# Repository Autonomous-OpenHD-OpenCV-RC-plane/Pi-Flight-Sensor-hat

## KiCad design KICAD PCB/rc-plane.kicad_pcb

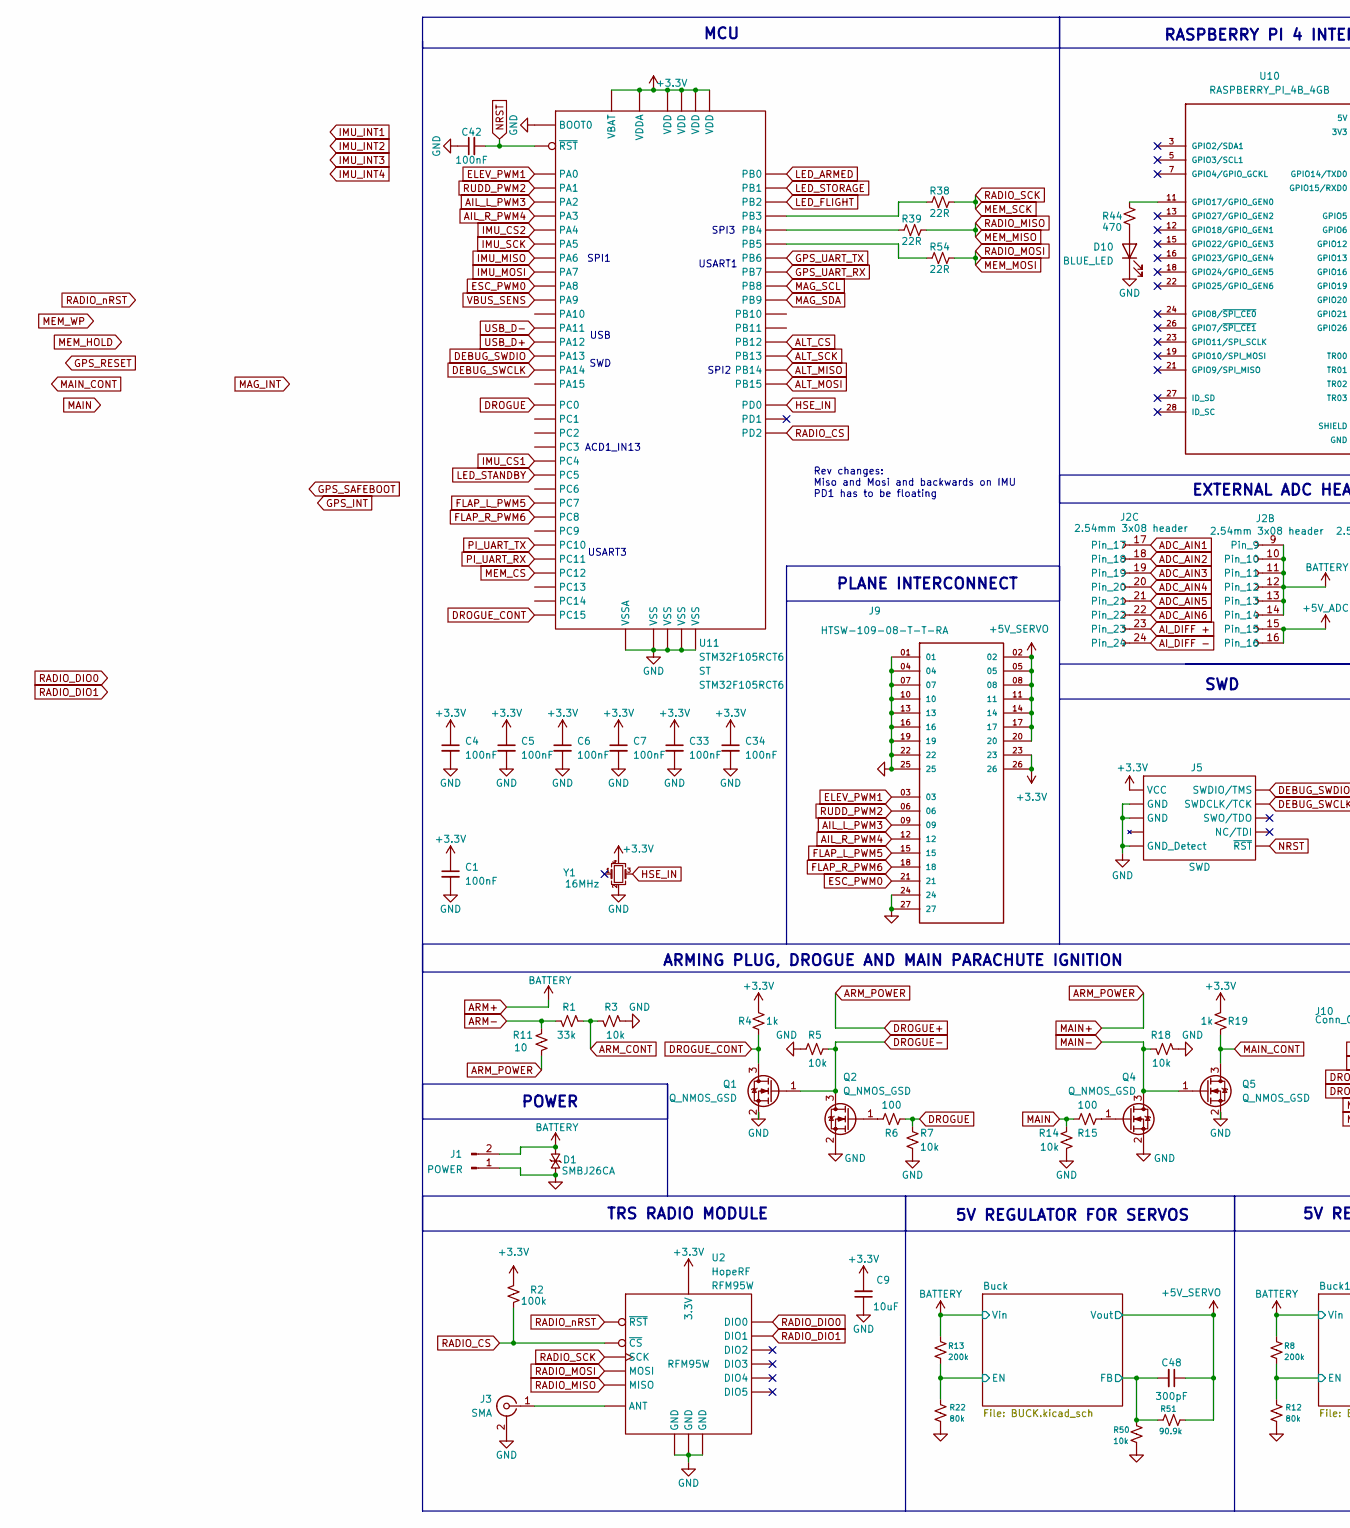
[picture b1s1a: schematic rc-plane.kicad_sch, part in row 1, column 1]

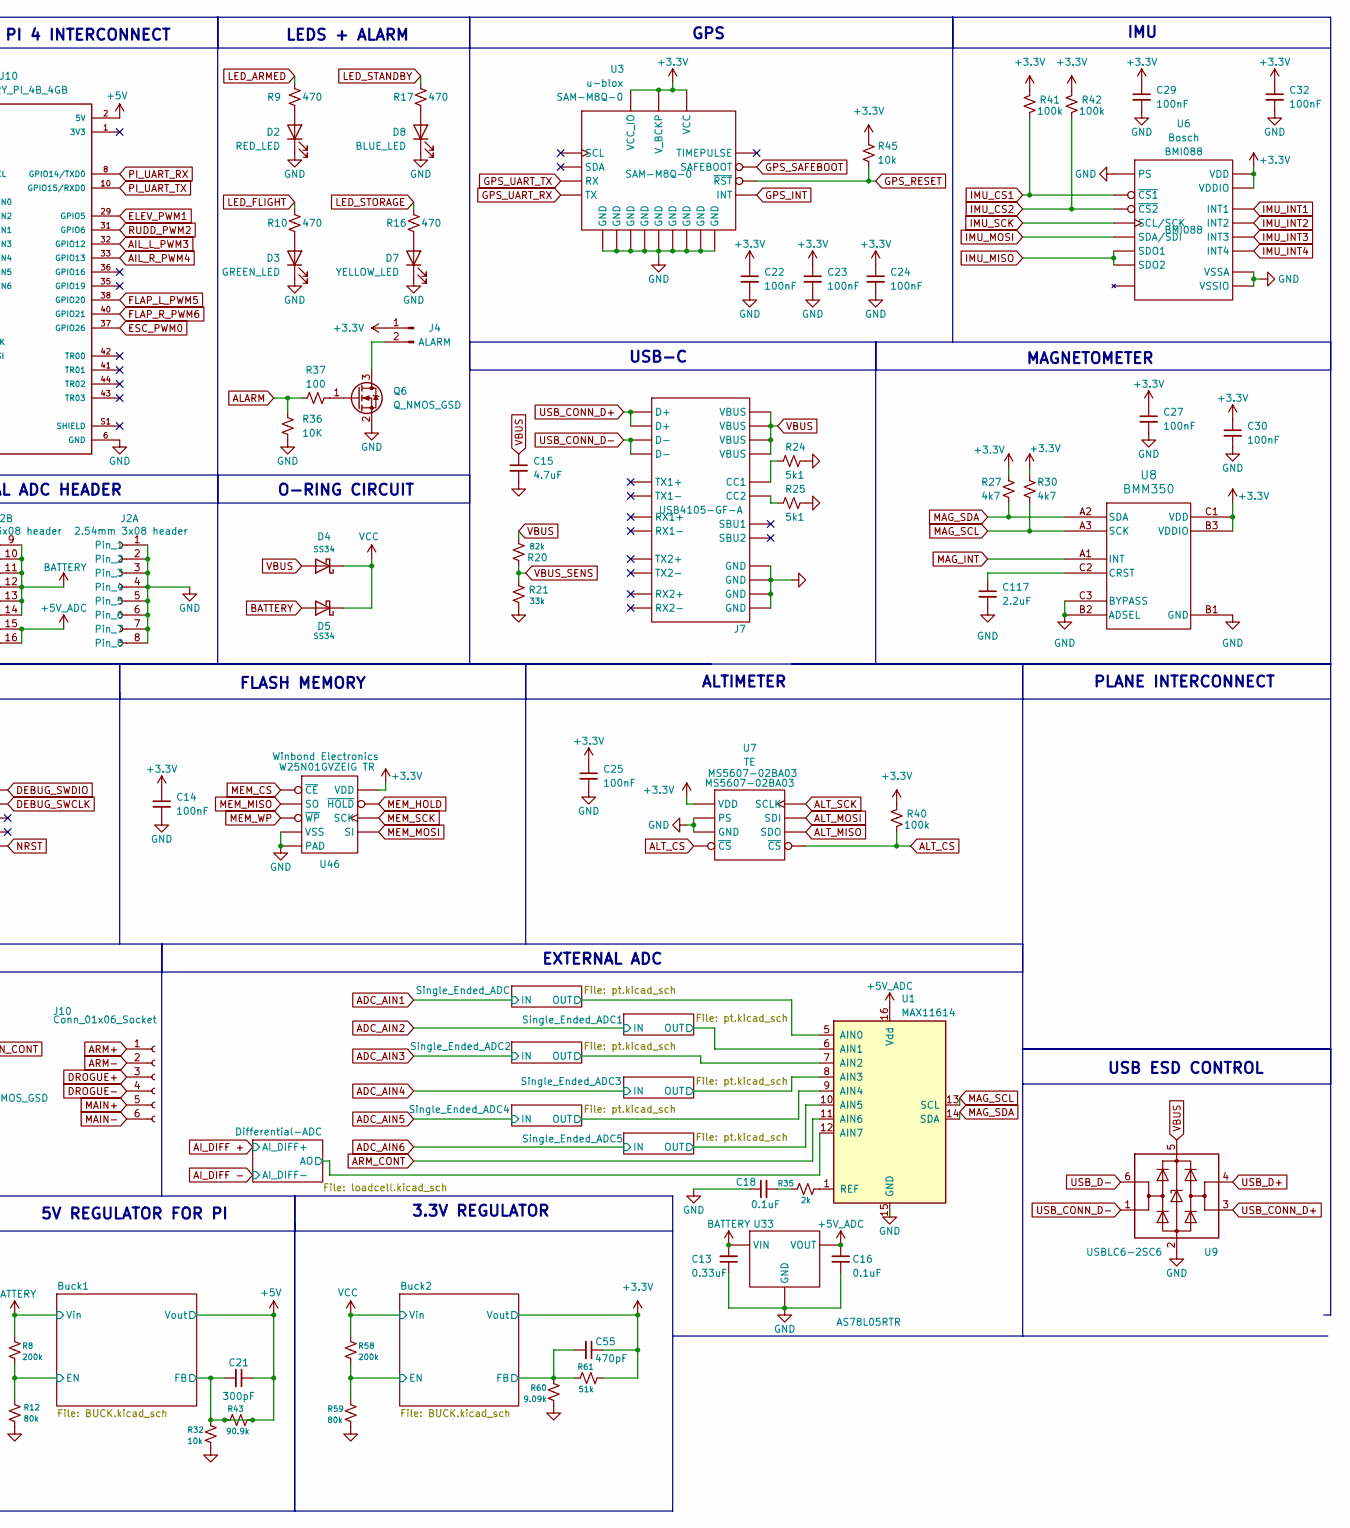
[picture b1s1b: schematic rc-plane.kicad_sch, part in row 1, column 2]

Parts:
C1, C4, C5, C6, C7, C14, C22, C23, C24, C25, C29, C32, C33, C34, C42: 100nF; C_0603_1608Metric; Part # Generic 0603 6.3V 100nF X7R MLCC
C9: 10uF; C_0603_1608Metric; Part # Generic 0603 6.3V 100nF X7R MLCC
C13: 0.33uF; C_0603_1608Metric; Part # Generic 22uF 35V X5R 1206 MLCC
C15: 4.7uF; C_0603_1608Metric; Part # Generic 0603 6.3V 4.7uF X7R MLCC
C16, C18: 0.1uF; C_0603_1608Metric; Part # Generic 22uF 35V X5R 1206 MLCC
C21, C48: 300pF; C_0603_1608Metric; Part # Generic 0603 6.3V 100nF X7R MLCC
C27, C30: 100nF; C_0402_1005Metric; Part # Generic CAP CER 0.1UF 6.3V X7R 0402
C55: 470pF; C_0603_1608Metric; Part # Generic 0603 6.3V 100nF X7R MLCC
C117: 2.2uF; C_0402_1005Metric; Part # Generic CAP CER 0.1UF 6.3V X7R 0402
D1: SMBJ26CA; D_SMB; PARTREV I2102; DigiKey_Part_Number SMBJ26CAFSCT-ND
D2: RED_LED; D_0603_1608Metric; Part # Generic Green LED
D3: GREEN_LED; D_0603_1608Metric; Part # Generic Green LED
D4, D5: SS34; D_SMA; Part # SS34
D7: YELLOW_LED; D_0603_1608Metric; Part # Generic Yellow LED
D8, D10: BLUE_LED; D_0603_1608Metric; Part # Generic Green LED
J1: POWER; AMASS_XT60PW-M_1x02_P7.20mm_Horizontal; Part # XT60PW-F
J2: 2.54mm 3x08 header; HX PZ2.54-3x8P ZZ 3x08 2.54mm THT header; Part # HX PZ2.54-3x8P ZZ
J3: SMA; SMA_Molex_73251-2200_Horizontal; Part # 0732512200
J4: ALARM; XDCR_SMT-0540-S-R; Part # CMI-0955-03TH
J5: SWD; PinHeader_2x05_P1.27mm_Vertical_SMD; Part # 4048
J7: USB4105-GF-A; USB_C_Receptacle_GCT_USB4105-xx-A_16P_TopMnt_Horizontal; Part # USB4105-GF-A
J9: HTSW-109-08-T-T-RA; SAMTEC_HTSW-109-08-T-T-RA; PARTREV R
J10: Conn_01x06_Socket; TerminalBlock_Xinya_XY308-2.54-6P_1x06_P2.54mm_Horizontal
Q1, Q2, Q4, Q5, Q6: Q_NMOS_GSD; TSOT-23; Part # WST3408
R1: 33k; R_0603_1608Metric; Part # Generic 0603 1k 1% Resistor
R2, R40, R41, R42: 100k; R_0603_1608Metric; Part # Generic 0603 1k 1% Resistor
R3: 10k; R_0603_1608Metric; Part # Generic 0603 3.3k 1% Resistor
R4, R19: 1k; R_0603_1608Metric; Part # Generic 0603 1k 1% Resistor
R5, R7, R14, R18: 10k; R_0603_1608Metric; Part # Generic 0603 10k 1% Resistor
R6, R15: 100; R_0603_1608Metric; Part # Generic 0603 100 1% Resistor
R8, R13, R58: 200k; R_0603_1608Metric
R9, R10, R16, R17, R44: 470; R_0603_1608Metric; Part # Generic 0603 470 1% Resistor
R11: 10; R_0603_1608Metric; Part # Generic 0603 1k 1% Resistor
R12, R22, R59: 80k; R_0603_1608Metric
R20: 82k; R_0603_1608Metric; Part # Generic 0603 33k 1% Resistor
R21: 33k; R_0603_1608Metric; Part # Generic 0603 82k 1% Resistor
R24, R25: 5k1; R_0603_1608Metric; Part # Generic 0603 5.1k 1% Resistor
R27, R30: 4k7; R_0402_1005Metric; Part # Generic RES SMD 4.7K OHM 1% 1/4W 0402
R32, R45, R50: 10k; R_0603_1608Metric
R35: 2k; R_0603_1608Metric
R36: 10K; R_0402_1005Metric; Part # Generic RES SMD 10K OHM 1% 1/4W 0402
R37: 100; R_0402_1005Metric; Part # Generic RES SMD 100 OHM 1% 1/4W 0402
R38, R39, R54: 22R; R_0402_1005Metric; Part # Generic RES SMD 4.7K OHM 1% 1/4W 0402
R43, R51: 90.9k; R_0603_1608Metric
R60: 9.09k; R_0603_1608Metric
R61: 51k; R_0603_1608Metric
U1: MAX11614; QSOP-16_3.9x4.9mm_P0.635mm
U2: RFM95W; Part # RFM95W
U3: SAM-M8Q-0; ublox_SAM-M8Q; Part # SAM-M8Q-0
U6: BMI088; Part # BMI088
U7: MS5607-02BA03; MS5607-02BA; Part # MS5607-02BA03
U8: BMM350; Part # BMM350
U9: USBLC6-2SC6; SOT-23-6; Part # USBLC6-2SC6
U10: RASPBERRY_PI_4B_4GB; MODULE_RASPBERRY_PI_4B_4GB; PARTREV 4
U11: STM32F105RCT6; LQFP-64_10x10mm_P0.5mm; Part # STM32F105RCT6
U33: AS78L05RTR; SOT-89-3
U46: W25N01GVZEIG TR; WSON-8-1EP_8x6mm_P1.27mm_EP3.4x4.3mm; Part # W25N01GVZEIG TR
Y1: 16MHz; Crystal_SMD_2520-4Pin_2.5x2.0mm; Part # ECS-1633-120-BN-TR

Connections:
+3.3V: C1.1, C4.1, C5.1, C6.1, C7.1, C9.2, C14.1, C22.1, C23.1, C24.1, C25.1, C27.1, C29.1, C30.1, C32.1, C33.1, C34.1, C55.1, J4.1, J5.1 (VCC), J9.23, J9.26, R2.2, R4.1, R19.1, R27.1, R30.1, R40.2, R41.2, R42.2, R45.1, R61.2, U2.13 (3.3V), U3.2 (VCC_IO), U3.3 (V_BCKP), U3.17 (VCC), U6.3 (VDD), U6.11 (VDDIO), U7.1 (VDD), U8.B3 (VDDIO), U8.C1 (VDD), U11.1 (VBAT), U11.13 (VDDA), U11.19 (VDD), U11.32 (VDD), U11.48 (VDD), U11.64 (VDD), U46.8 (VDD), Y1.4; also elsewhere on the board
+5V_ADC: C16.1, J2.15, J2.16, U1.16 (Vdd), U33.3 (VOUT); also elsewhere on the board
+5V_SERVO: C48.1, J9.02, J9.05, J9.08, J9.11, J9.14, J9.17, J9.20, R51.2; also elsewhere on the board
/Buck1/EN: R8.2, R12.1; also elsewhere on the board
/Buck2/EN: R58.2, R59.1; also elsewhere on the board
/Buck2/FB: C55.2, R60.1, R61.1; also elsewhere on the board
/Buck/EN: R13.2, R22.1; also elsewhere on the board
/Buck/FB: C48.2, R50.1, R51.1; also elsewhere on the board
/Differential-ADC/AO: U1.12 (AIN7); also elsewhere on the board
/Single_Ended_ADC1/OUT: U1.6 (AIN1); also elsewhere on the board
/Single_Ended_ADC2/OUT: U1.7 (AIN2); also elsewhere on the board
/Single_Ended_ADC3/OUT: U1.8 (AIN3); also elsewhere on the board
/Single_Ended_ADC4/OUT: U1.9 (AIN4); also elsewhere on the board
/Single_Ended_ADC5/OUT: U1.10 (AIN5); also elsewhere on the board
/Single_Ended_ADC/OUT: U1.5 (AIN0); also elsewhere on the board
ADC_AIN1: J2.17; also elsewhere on the board
ADC_AIN2: J2.18; also elsewhere on the board
ADC_AIN3: J2.19; also elsewhere on the board
ADC_AIN4: J2.20; also elsewhere on the board
ADC_AIN5: J2.21; also elsewhere on the board
ADC_AIN6: J2.22; also elsewhere on the board
AIL_L_PWM3: J9.09, U10.32 (GPIO12), U11.16 (PA2)
AIL_R_PWM4: J9.12, U10.33 (GPIO13), U11.17 (PA3)
AI_DIFF +: J2.23; also elsewhere on the board
AI_DIFF -: J2.24; also elsewhere on the board
ALARM: R36.2, R37.1
ALT_CS: R40.1, U7.4 (~CS), U7.5 (~CS), U11.33 (PB12)
ALT_MISO: U7.6 (SDO), U11.35 (PB14)
ALT_MOSI: U7.7 (SDI), U11.36 (PB15)
ALT_SCK: U7.8 (SCLK), U11.34 (PB13)
ARM+: C13.2, D1.1, D5.2 (A), J1.2, J2.9, J2.10, J2.11, J2.12, J2.13, J2.14, J10.1, R8.1, R13.1, U33.1 (VIN); also elsewhere on the board
ARM-: J10.2, R1.1, R11.2
ARM_CONT: R1.2, R3.1, U1.11 (AIN6)
ARM_POWER: J10.3, J10.5, R11.1
DEBUG_SWCLK: J5.4 (SWDCLK/TCK), U11.49 (PA14)
DEBUG_SWDIO: J5.2 (SWDIO/TMS), U11.46 (PA13)
DROGUE: R6.2, R7.1, U11.8 (PC0)
DROGUE-: J10.4, Q1.1 (G), Q2.3 (D), R5.1
DROGUE_CONT: Q1.3 (D), R4.2, U11.4 (PC15)
ELEV_PWM1: J9.03, U10.29 (GPIO5), U11.14 (PA0)
ESC_PWM0: J9.21, U10.37 (GPIO26), U11.41 (PA8)
FLAP_L_PWM5: J9.15, U10.38 (GPIO20), U11.38 (PC7)
FLAP_R_PWM6: J9.18, U10.40 (GPIO21), U11.39 (PC8)
GND: C1.2, C4.2, C5.2, C6.2, C7.2, C9.1, C13.1, C14.2, C15.2, C16.2, C18.1, C22.2, C23.2, C24.2, C25.2, C27.2, C29.2, C30.2, C32.2, C33.2, C34.2, C42.1, C117.2, D1.2, D2.1 (K), D3.1 (K), D7.1 (K), D8.1 (K), D10.1 (K), J1.1, J2.1, J2.2, J2.3, J2.4, J2.5, J2.6, J2.7, J2.8, J3.2 (Ext), J5.3 (GND), J5.5 (GND), J5.9 (GND_Detect), J7.A1 (GND), J7.A12 (GND), J7.B1 (GND), J7.B12 (GND), J9.01, J9.04, J9.07, J9.10, J9.13, J9.16, J9.19, J9.22, J9.24, J9.25, J9.27, Q1.2 (S), Q2.2 (S), Q4.2 (S), Q5.2 (S), Q6.2 (S), R3.2, R5.2, R7.2, R12.2, R14.2, R18.2, R21.1, R22.2, R24.1, R25.1, R32.2, R36.1, R50.2, R59.2, R60.2, U1.15 (GND), U2.1 (GND), U2.8 (GND), U2.10 (GND), U3.1 (GND), U3.4 (GND), U3.5 (GND), U3.6 (GND), U3.10 (GND), U3.11 (GND), U3.15 (GND), U3.16 (GND), U3.20 (GND), U6.4 (VSSA), U6.6 (VSSIO), U6.7 (PS), U7.2 (PS), U7.3 (GND), U8.B1 (GND), U8.B2 (ADSEL), U8.C3 (BYPASS), U9.2 (GND), U10.6 (GND), U10.9 (GND), U10.14 (GND), U10.20 (GND), U10.25 (GND), U10.30 (GND), U10.34 (GND), U10.39 (GND), U11.12 (VSSA), U11.18 (VSS), U11.31 (VSS), U11.47 (VSS), U11.60 (BOOT0), U11.63 (VSS), U33.2 (GND), U46.4 (VSS), U46.9 (PAD), Y1.2; also elsewhere on the board
GPS_INT: U3.19 (INT), U11.2 (PC13)
GPS_RESET: R45.2, U3.18 (~RST), U11.40 (PC9)
GPS_SAFEBOOT: U3.8 (SAFEBOOT), U11.3 (PC14)
GPS_UART_RX: U3.13 (TX), U11.59 (PB7)
GPS_UART_TX: U3.14 (RX), U11.58 (PB6)
HSE_IN: U11.5 (PD0), Y1.3
IMU_CS1: R41.1, U6.14 (~CS1), U11.24 (PC4)
IMU_CS2: R42.1, U6.5 (~CS2), U11.20 (PA4)
IMU_INT1: U6.16 (INT1)
IMU_INT2: U6.1 (INT2)
IMU_INT3: U6.12 (INT3)
IMU_INT4: U6.13 (INT4)
IMU_MISO: U6.10 (SDO2), U6.15 (SDO1), U11.22 (PA6)
IMU_MOSI: U6.9 (SDA/SDI), U11.23 (PA7)
IMU_SCK: U6.8 (SCL/SCK), U11.21 (PA5)
LED_ARMED: R9.1, U11.26 (PB0)
LED_FLIGHT: R10.1, U11.28 (PB2)
LED_STANDBY: R17.1, U11.25 (PC5)
LED_STORAGE: R16.1, U11.27 (PB1)
MAG_INT: U8.A1 (INT), U11.11 (PC3)
MAIN: R14.1, R15.1, U11.10 (PC2)
MAIN-: J10.6, Q4.3 (D), Q5.1 (G), R18.1
MAIN_CONT: Q5.3 (D), R19.2, U11.9 (PC1)
MEM_CS: U11.53 (PC12), U46.1 (~CE)
MEM_HOLD: U46.7 (~HOLD)
MEM_MISO: R39.2, U2.2 (MISO), U46.2 (SO)
MEM_MOSI: R54.2, U2.3 (MOSI), U46.5 (SI)
MEM_SCK: R38.2, U2.4 (SCK), U46.6 (SCK)
MEM_WP: U46.3 (~WP)
NRST: C42.2, J5.10 (~RST), U11.7 (~RST)
unnamed: C18.2, R35.1
unnamed: D2.2 (A), R9.2
unnamed: D3.2 (A), R10.2
unnamed: D7.2 (A), R16.2
unnamed: D8.2 (A), R17.2
unnamed: D10.2 (A), R44.2
unnamed: J3.1 (In), U2.9 (ANT)
unnamed: J4.2, Q6.3 (D)
unnamed: J7.A5 (CC1), R24.2
unnamed: J7.B5 (CC2), R25.2
unnamed: Q2.1 (G), R6.1
unnamed: Q4.1 (G), R15.2
unnamed: Q6.1 (G), R37.2
unnamed: R35.2, U1.1 (REF)
unnamed: C117.1, U8.C2 (CRST)
unnamed: R44.1, U10.11 (GPIO17/GPIO_GEN0)
unnamed: R38.1, U11.55 (PB3)
unnamed: R39.1, U11.56 (PB4)
unnamed: R54.1, U11.57 (PB5)
PI_UART_RX: U10.8 (GPIO14/TXD0), U11.52 (PC11)
PI_UART_TX: U10.10 (GPIO15/RXD0), U11.51 (PC10)
RADIO_CS: R2.1, U2.5 (~CS), U11.54 (PD2)
RADIO_DIO0: U2.14 (DIO0), U11.29 (PB10)
RADIO_DIO1: U2.15 (DIO1), U11.30 (PB11)
RADIO_nRST: U2.6 (~RST), U11.37 (PC6)
RUDD_PWM2: J9.06, U10.31 (GPIO6), U11.15 (PA1)
SCL: R30.2, U1.13 (SCL), U8.A3 (SCK), U11.61 (PB8)
SDA: R27.2, U1.14 (SDA), U8.A2 (SDA), U11.62 (PB9)
USB_CONN_D+: J7.A6 (D+), J7.B6 (D+), U9.3 (I/O2)
USB_CONN_D-: J7.A7 (D-), J7.B7 (D-), U9.1 (I/O1)
USB_D+: U9.4 (I/O2), U11.45 (PA12)
USB_D-: U9.6 (I/O1), U11.44 (PA11)
VBUS: C15.1, D4.2 (A), J7.A4 (VBUS), J7.A9 (VBUS), J7.B4 (VBUS), J7.B9 (VBUS), R20.1, U9.5 (VBUS)
VBUS_SENS: R20.2, R21.2, U11.42 (PA9)
VCC: D4.1 (K), D5.1 (K), R58.1; also elsewhere on the board

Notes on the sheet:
USART1
POWER
TRS RADIO MODULE
PLANE INTERCONNECT
USB ESD CONTROL
Rev changes: Miso and Mosi and backwards on IMU PD1 has to be floating
USART3
SWD
MCU
ALTIMETER
5V REGULATOR FOR SERVOS
SPI2
SWD
O-RING CIRCUIT
GPS
IMU
EXTERNAL ADC HEADER
MAGNETOMETER
FLASH MEMORY
RASPBERRY PI 4 INTERCONNECT
SPI1
USB-C
USB
LEDS + ALARM
ARMING PLUG, DROGUE AND MAIN PARACHUTE IGNITION
5V REGULATOR FOR PI
SPI3
ACD1_IN13
EXTERNAL ADC
3.3V REGULATOR

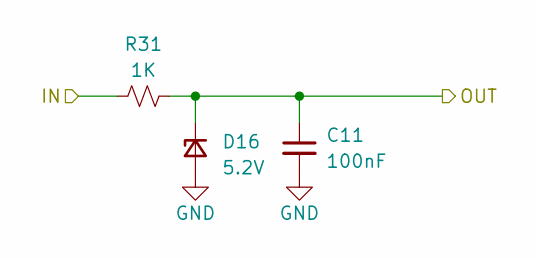
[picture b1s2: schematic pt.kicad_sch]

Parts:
C11: 100nF; C_0402_1005Metric; Part # Generic CAP CER 0.1UF 6.3V X7R 0402
D16: 5.2V; D_SOD-882; Part # BZT52C3V9LP-7
R31: 1K; R_0402_1005Metric; Part # Generic RES SMD 1K OHM 1% 1/16W 0402

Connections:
/Single_Ended_ADC/OUT: C11.1, D16.1 (K), R31.2; also elsewhere on the board
ADC_AIN1: R31.1; also elsewhere on the board
GND: C11.2, D16.2 (A); also elsewhere on the board

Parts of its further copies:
C2, C3, C8, C10, C12: 100nF; C_0402_1005Metric; Part # Generic CAP CER 0.1UF 6.3V X7R 0402
R23, R26, R28, R29, R33: 1K; R_0402_1005Metric; Part # Generic RES SMD 1K OHM 1% 1/16W 0402

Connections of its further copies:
/Single_Ended_ADC1/OUT: C2.1, R23.2; also elsewhere on the board
/Single_Ended_ADC2/OUT: C3.1, R26.2; also elsewhere on the board
/Single_Ended_ADC3/OUT: C8.1, R28.2; also elsewhere on the board
/Single_Ended_ADC4/OUT: C10.1, R29.2; also elsewhere on the board
/Single_Ended_ADC5/OUT: C12.1, R33.2; also elsewhere on the board
ADC_AIN2: R23.1; also elsewhere on the board
ADC_AIN3: R26.1; also elsewhere on the board
ADC_AIN4: R28.1; also elsewhere on the board
ADC_AIN5: R29.1; also elsewhere on the board
ADC_AIN6: R33.1; also elsewhere on the board
GND: C2.2, C3.2, C8.2, C10.2, C12.2; also elsewhere on the board

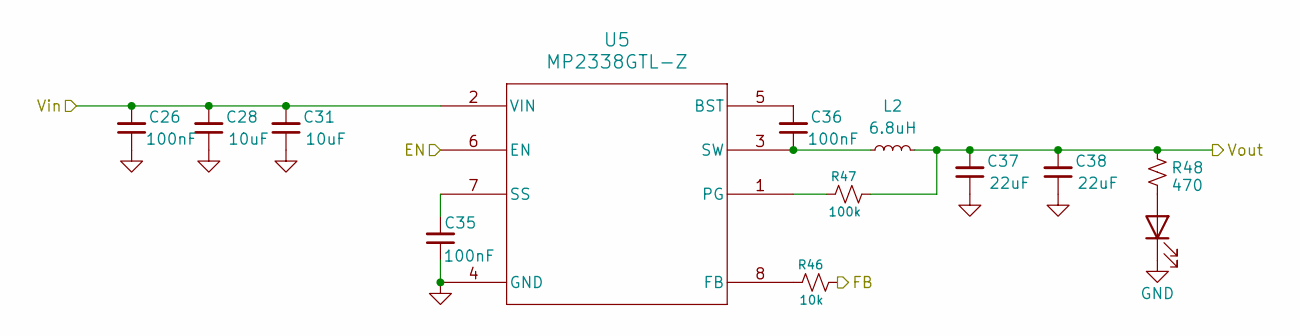
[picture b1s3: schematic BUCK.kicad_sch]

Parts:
C26, C35, C36: 100nF; C_0603_1608Metric; Part # Generic 0603 6.3V 100nF X7R MLCC
C28, C31: 10uF; C_0603_1608Metric; Part # Generic 0603 6.3V 100nF X7R MLCC
C37, C38: 22uF; C_0603_1608Metric; Part # Generic 0603 6.3V 100nF X7R MLCC
D11: BLUE_LED; D_0603_1608Metric; Part # Generic Green LED
L2: 6.8uH; IND_VLS6045EX-6R8M; Part # VLS6045EX-6R8M
R46: 10k; R_0603_1608Metric
R47: 100k; R_0603_1608Metric
R48: 470; R_0603_1608Metric; Part # Generic 0603 470 1% Resistor
U5: MP2338GTL-Z; SOT583_MP2338_MNP; Part # MP2338GTL-P

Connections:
/Buck1/EN: U5.6 (EN); also elsewhere on the board
ARM+: C26.2, C28.2, C31.2, U5.2 (VIN); also elsewhere on the board
GND: C26.1, C28.1, C31.1, C35.1, C37.1, C38.1, D11.1 (K), U5.4 (GND); also elsewhere on the board
unnamed: D11.2 (A), R48.2
unnamed: C36.2, U5.5 (BST)
unnamed: R46.1, U5.8 (FB)
unnamed: R47.1, U5.1 (PG)
unnamed: C35.2, U5.7 (SS)
unnamed: C36.1, L2.1, U5.3 (SW)

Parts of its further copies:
C39, C43, C44, C46, C51, C52: 100nF; C_0603_1608Metric; Part # Generic 0603 6.3V 100nF X7R MLCC
C40, C41, C49, C50: 10uF; C_0603_1608Metric; Part # Generic 0603 6.3V 100nF X7R MLCC
C45, C47, C53, C54: 22uF; C_0603_1608Metric; Part # Generic 0603 6.3V 100nF X7R MLCC
D12, D13: BLUE_LED; D_0603_1608Metric; Part # Generic Green LED
L3, L4: 6.8uH; IND_VLS6045EX-6R8M; Part # VLS6045EX-6R8M
R49, R53: 10k; R_0603_1608Metric
R52, R55: 100k; R_0603_1608Metric
R56, R57: 470; R_0603_1608Metric; Part # Generic 0603 470 1% Resistor
U12, U13: MP2338GTL-Z; SOT583_MP2338_MNP; Part # MP2338GTL-P

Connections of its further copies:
+3.3V: C53.2, C54.2, L4.2, R55.2, R57.1; also elsewhere on the board
+5V_SERVO: C45.2, C47.2, L3.2, R52.2, R56.1; also elsewhere on the board
/Buck2/EN: U13.6 (EN); also elsewhere on the board
/Buck2/FB: R49.2; also elsewhere on the board
/Buck/EN: U12.6 (EN); also elsewhere on the board
/Buck/FB: R53.2; also elsewhere on the board
ARM+: C39.2, C40.2, C41.2, U12.2 (VIN); also elsewhere on the board
GND: C39.1, C40.1, C41.1, C43.1, C45.1, C46.1, C47.1, C49.1, C50.1, C51.1, C53.1, C54.1, D12.1 (K), D13.1 (K), U12.4 (GND), U13.4 (GND); also elsewhere on the board
unnamed: D12.2 (A), R56.2
unnamed: D13.2 (A), R57.2
unnamed: C44.2, U12.5 (BST)
unnamed: R53.1, U12.8 (FB)
unnamed: R52.1, U12.1 (PG)
unnamed: C43.2, U12.7 (SS)
unnamed: C44.1, L3.1, U12.3 (SW)
unnamed: C52.2, U13.5 (BST)
unnamed: R49.1, U13.8 (FB)
unnamed: R55.1, U13.1 (PG)
unnamed: C51.2, U13.7 (SS)
unnamed: C52.1, L4.1, U13.3 (SW)
VCC: C46.2, C49.2, C50.2, U13.2 (VIN); also elsewhere on the board

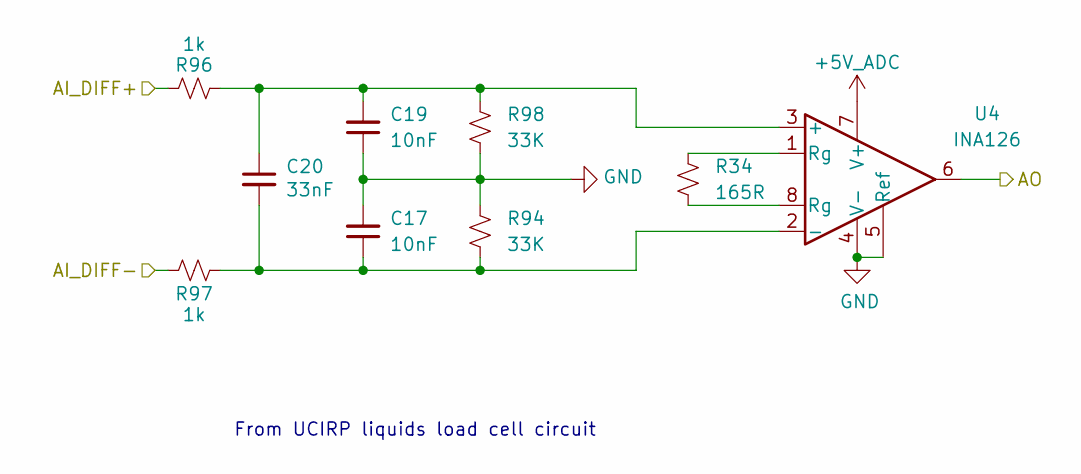
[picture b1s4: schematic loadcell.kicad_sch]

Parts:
C17, C19: 10nF; C_0603_1608Metric
C20: 33nF; C_0603_1608Metric
R34: 165R; R_0603_1608Metric; Part # Generic 33K 1% 0402 Resistor
R94, R98: 33K; R_0603_1608Metric; Part # Generic 33K 1% 0402 Resistor
R96, R97: 1k; R_0603_1608Metric
U4: INA126; SOIC-8_3.9x4.9mm_P1.27mm

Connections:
+5V_ADC: U4.7 (V+); also elsewhere on the board
/Differential-ADC/AO: U4.6; also elsewhere on the board
AI_DIFF +: R96.2; also elsewhere on the board
AI_DIFF -: R97.1; also elsewhere on the board
GND: C17.2, C19.1, R94.2, R98.1, U4.4 (V-), U4.5 (Ref); also elsewhere on the board
unnamed: R34.1, U4.8 (Rg)
unnamed: R34.2, U4.1 (Rg)
unnamed: C19.2, C20.1, R96.1, R98.2, U4.3 (+)
unnamed: C17.1, C20.2, R94.1, R97.2, U4.2 (-)

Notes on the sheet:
From UCIRP liquids load cell circuit

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
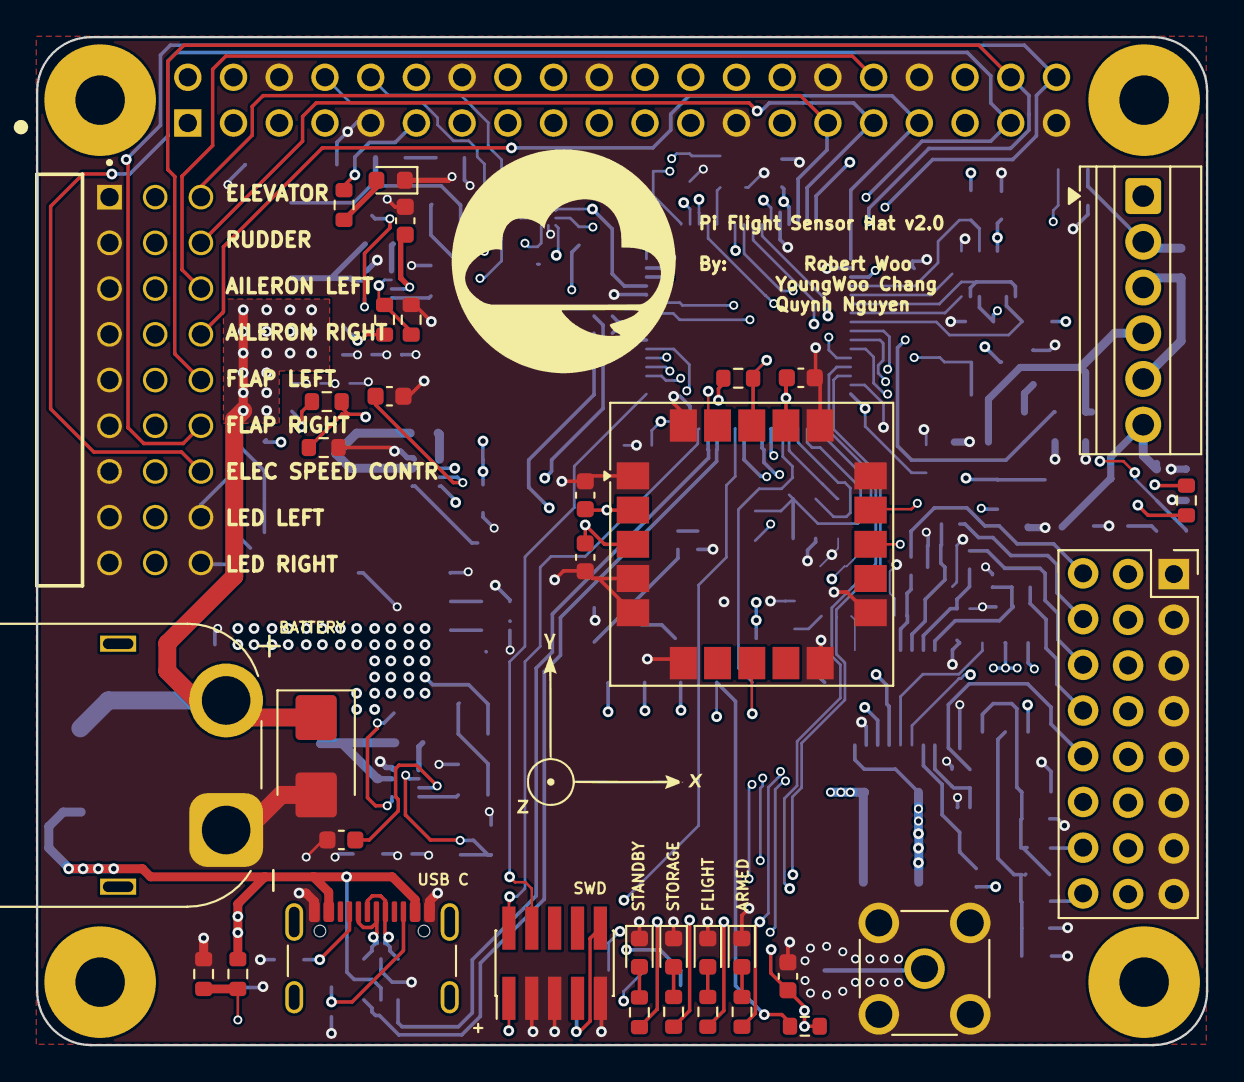
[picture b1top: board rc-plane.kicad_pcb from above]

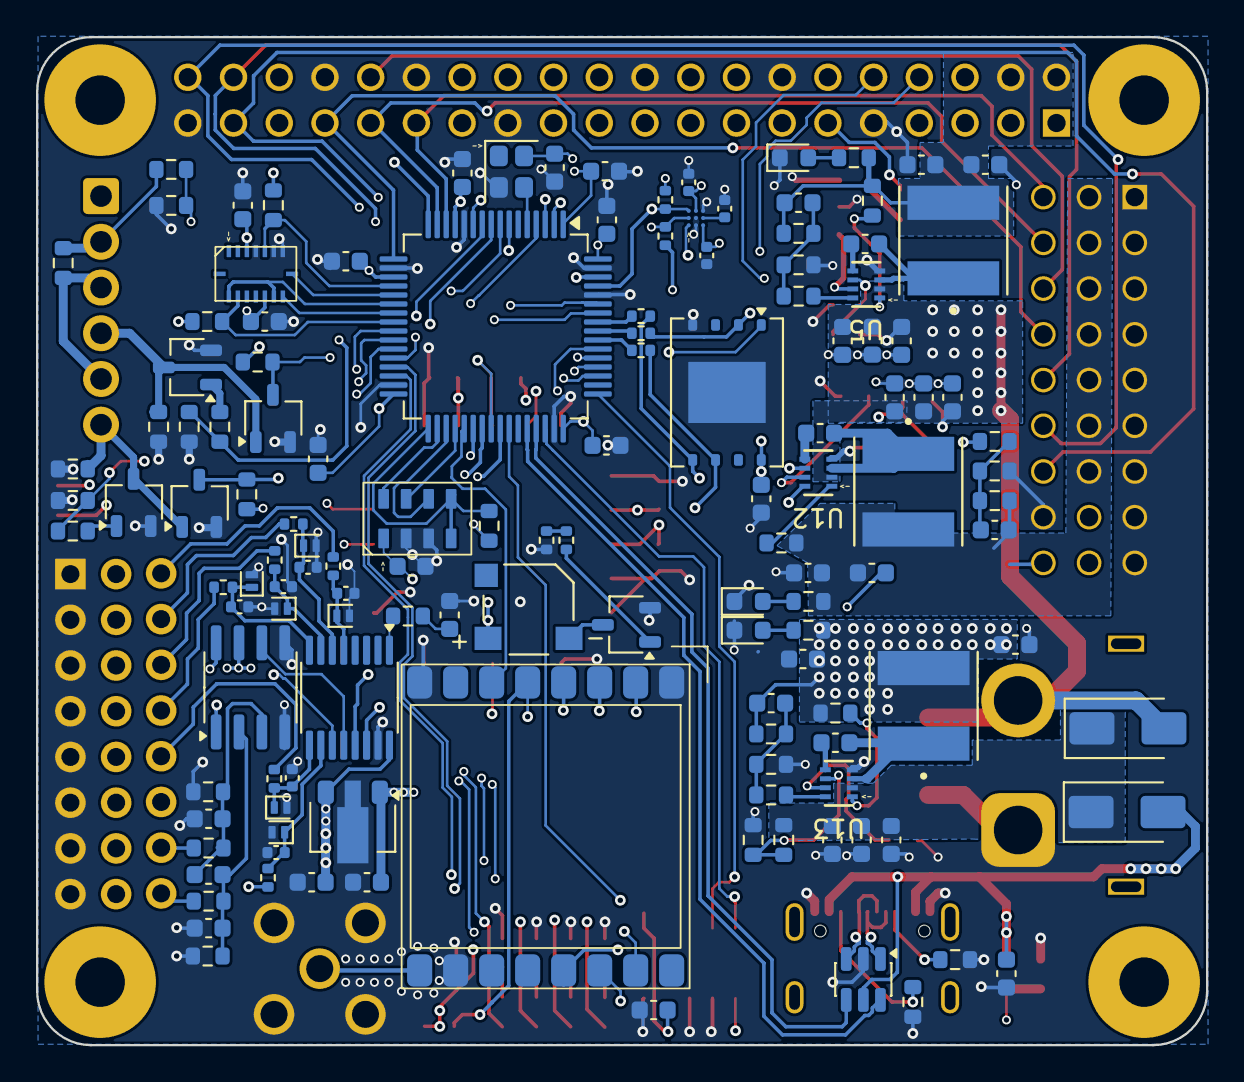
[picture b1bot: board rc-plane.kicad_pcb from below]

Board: 4 copper layers, 65.0 x 56.0 mm, 170 parts (134 on the bottom side), 127 nets.

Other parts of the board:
D6, D9, D14, D15, D17: 3.9V; D_SOD-882

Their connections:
/Single_Ended_ADC1/OUT: D6.1 (K); also elsewhere on the board
/Single_Ended_ADC2/OUT: D9.1 (K); also elsewhere on the board
/Single_Ended_ADC3/OUT: D14.1 (K); also elsewhere on the board
/Single_Ended_ADC4/OUT: D15.1 (K); also elsewhere on the board
/Single_Ended_ADC5/OUT: D17.1 (K); also elsewhere on the board
GND: D6.2 (A), D9.2 (A), D14.2 (A), D15.2 (A), D17.2 (A); also elsewhere on the board

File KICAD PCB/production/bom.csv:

Designator,Footprint,Quantity,Value,LCSC Part #
"C1, C14, C22, C23, C24, C25, C26, C29, C32, C33, C34, C35, C36, C39, C4, C42, C43, C44, C46, C5, C51, C52, C6, C7",0603,24,100nF,
"C10, C11, C12, C2, C27, C3, C30, C8",0402,8,100nF,
C117,0402,1,2.2uF,
C13,0603,1,0.33uF,
C15,0603,1,4.7uF,
"C16, C18",0603,2,0.1uF,
"C17, C19",0603,2,10nF,
C20,0603,1,33nF,
"C21, C48",0603,2,300pF,
"C28, C31, C40, C41, C49, C50, C9",0603,7,10uF,
"C37, C38, C45, C47, C53, C54",0603,6,22uF,
C55,0603,1,470pF,
D1,D_SMB,1,SMBJ26CA,
"D10, D11, D12, D13, D8",0603,5,BLUE_LED,
"D14, D15, D16, D17, D6, D9",D_SOD-882,6,3.9V,
D2,0603,1,RED_LED,
D3,0603,1,GREEN_LED,
"D4, D5",D_SMA,2,SS34,
D7,0603,1,YELLOW_LED,
J1,AMASS_XT60PW-M_1x02_P7.20mm_Horizontal,1,POWER,
J10,TerminalBlock_Xinya_XY308-2.54-6P_1x06_P2.54mm_Horizontal,1,Conn_01x06_Socket,
J2,HX PZ2.54-3x8P ZZ 3x08 2.54mm THT header,1,2.54mm 3x08 header,
J4,XDCR_SMT-0540-S-R,1,ALARM,
J5,PinHeader_2x05_P1.27mm_Vertical_SMD,1,SWD,
J7,USB_C_Receptacle_GCT_USB4105-xx-A_16P_TopMnt_Horizontal,1,USB4105-GF-A,
J9,SAMTEC_HTSW-109-08-T-T-RA,1,HTSW-109-08-T-T-RA,
"L2, L3, L4",IND_VLS6045EX-6R8M,3,6.8uH,
"Q1, Q2, Q4, Q5, Q6",TSOT-23,5,Q_NMOS_GSD,
"R1, R21, R94, R98",0603,4,33k,
"R10, R16, R17, R44, R48, R56, R57, R9",0603,8,470,
R11,0603,1,10,
"R12, R22, R59",0603,3,80k,
"R13, R58, R8",0603,3,200k,
"R14, R18, R3, R32, R45, R46, R49, R5, R50, R53, R7",0603,11,10k,
"R15, R6",0603,2,100,
"R19, R4, R96, R97",0603,4,1k,
"R2, R40, R41, R42, R47, R52, R55",0603,7,100k,
R20,0603,1,82k,
"R23, R26, R28, R29, R31, R33",0402,6,1K,
"R24, R25",0603,2,5k1,
"R27, R30",0402,2,4k7,
R34,0603,1,165R,
R35,0603,1,2k,
R36,0402,1,10K,
R37,0402,1,100,
"R38, R39, R54",0402,3,22R,
"R43, R51",0603,2,90.9k,
R60,0603,1,9.09k,
R61,0603,1,51k,
U1,QSOP-16_3.9x4.9mm_P0.635mm,1,MAX11614,
U11,LQFP-64_10x10mm_P0.5mm,1,STM32F105RCT6,
"U12, U13, U5",SOT583_MP2338_MNP,3,MP2338GTL-Z,
U3,ublox_SAM-M8Q,1,SAM-M8Q-0,
U33,SOT-89-3,1,AS78L05RTR,
U4,SOIC-8_3.9x4.9mm_P1.27mm,1,INA126,
U46,WSON-8-1EP_8x6mm_P1.27mm_EP3.4x4.3mm,1,W25N01GVZEIG TR,
U6,BMI088,1,BMI088,
U7,MS5607-02BA,1,MS5607-02BA03,
U8,BMM350,1,BMM350,
U9,SOT-23-6,1,USBLC6-2SC6,
Y1,Crystal_SMD_2520-4Pin_2.5x2.0mm,1,16MHz,

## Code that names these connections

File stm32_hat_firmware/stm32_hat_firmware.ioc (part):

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Mcu.Name=STM32F105R(8-B-C)Tx
Mcu.Package=LQFP64
Mcu.UserName=STM32F105RCTx
PA0-WKUP.GPIOParameters=GPIO_Label
PA0-WKUP.GPIO_Label=ELEV_PWM1
PA0-WKUP.Signal=S_TIM2_CH1_ETR
PA1.GPIOParameters=GPIO_Label
PA1.GPIO_Label=RUDD_PWM2
PA1.Signal=S_TIM2_CH2
PA11.Mode=Device_Only
PA11.Signal=USB_OTG_FS_DM
PA12.Mode=Device_Only
PA12.Signal=USB_OTG_FS_DP
PA13.Mode=Serial_Wire
PA13.Signal=SYS_JTMS-SWDIO
PA14.Mode=Serial_Wire
PA14.Signal=SYS_JTCK-SWCLK
PA2.GPIOParameters=GPIO_Label
PA2.GPIO_Label=AIL_L_PWM3
PA2.Signal=S_TIM2_CH3
PA3.GPIOParameters=GPIO_Label
PA3.GPIO_Label=AIL_R_PWM4
PA3.Signal=S_TIM2_CH4
PA4.GPIOParameters=GPIO_Label
PA4.GPIO_Label=IMU_CS2
PA4.Signal=GPIO_Output
PA5.GPIOParameters=GPIO_Label
PA5.GPIO_Label=IMU_SCK
PA5.Mode=Full_Duplex_Master
PA5.Signal=SPI1_SCK
PA6.GPIOParameters=GPIO_Label
PA6.GPIO_Label=IMU_MISO
PA6.Mode=Full_Duplex_Master
PA6.Signal=SPI1_MISO
PA7.GPIOParameters=GPIO_Label
PA7.GPIO_Label=IMUMOSI
PA7.Mode=Full_Duplex_Master
PA7.Signal=SPI1_MOSI
PA8.GPIOParameters=GPIO_Label
PA8.GPIO_Label=ESC_PWM0
PA8.Signal=S_TIM1_CH1
PA9.Mode=Activate_VBUS
PA9.Signal=USB_OTG_FS_VBUS
PB0.GPIOParameters=GPIO_Label
PB0.GPIO_Label=LED_ARMED
PB0.Signal=GPIO_Output
PB1.GPIOParameters=GPIO_Label
PB1.GPIO_Label=LED_STORAGE
PB1.Signal=GPIO_Output
PB10.GPIOParameters=GPIO_Label
PB10.GPIO_Label=EN_SERVO
PB10.Signal=GPIO_Output
PB11.GPIOParameters=GPIO_Label
PB11.GPIO_Label=EN_PI
PB11.Signal=GPIO_Output
PB12.GPIOParameters=GPIO_Label
PB12.GPIO_Label=ALT_CS
PB12.Signal=GPIO_Output
PB13.GPIOParameters=GPIO_Label
PB13.GPIO_Label=ALT_SCK
PB13.Mode=Full_Duplex_Master
PB13.Signal=SPI2_SCK
PB14.GPIOParameters=GPIO_Label
PB14.GPIO_Label=ALT_MISO
PB14.Mode=Full_Duplex_Master
PB14.Signal=SPI2_MISO
PB15.GPIOParameters=GPIO_Label
PB15.GPIO_Label=ALT_MOSI
PB15.Mode=Full_Duplex_Master
PB15.Signal=SPI2_MOSI
PB2.GPIOParameters=GPIO_Label
PB2.GPIO_Label=LED_FLIGHT
PB2.Signal=GPIO_Output
PB3.GPIOParameters=GPIO_Label
PB3.GPIO_Label=SCK3
PB3.Mode=Full_Duplex_Master
PB3.Signal=SPI3_SCK
PB4.GPIOParameters=GPIO_Label
PB4.GPIO_Label=MISO3
PB4.Mode=Full_Duplex_Master
PB4.Signal=SPI3_MISO
PB5.GPIOParameters=GPIO_Label
PB5.GPIO_Label=MOSI3
PB5.Mode=Full_Duplex_Master
PB5.Signal=SPI3_MOSI
PB6.GPIOParameters=GPIO_Label
PB6.GPIO_Label=GPS_UART_TX
PB6.Mode=Asynchronous
PB6.Signal=USART1_TX
PB7.GPIOParameters=GPIO_Label
PB7.GPIO_Label=GPS_UART_RX
PB7.Mode=Asynchronous
PB7.Signal=USART1_RX
PB8.GPIOParameters=GPIO_Label
PB8.GPIO_Label=SCL1
PB8.Mode=I2C
PB8.Signal=I2C1_SCL
PB9.GPIOParameters=GPIO_Label
PB9.GPIO_Label=SDA1
PB9.Mode=I2C
PB9.Signal=I2C1_SDA
PC0.GPIOParameters=GPIO_Label
PC0.GPIO_Label=DROGUE
PC0.Signal=GPIO_Output
PC1.GPIOParameters=GPIO_Label
PC1.GPIO_Label=MAIN_CONT
PC1.Signal=GPIO_Input
PC10.GPIOParameters=GPIO_Label
PC10.GPIO_Label=PI_UART_TX
PC10.Mode=Asynchronous
PC10.Signal=USART3_TX
PC11.GPIOParameters=GPIO_Label
PC11.GPIO_Label=PI_UART_RX
PC11.Mode=Asynchronous
PC11.Signal=USART3_RX
PC12.GPIOParameters=GPIO_Label
PC12.GPIO_Label=MEM_CS
PC12.Signal=GPIO_Output
PC13-TAMPER-RTC.GPIOParameters=GPIO_Label
PC13-TAMPER-RTC.GPIO_Label=GPS_INT
PC13-TAMPER-RTC.Signal=GPIO_Input
PC14-OSC32_IN.GPIOParameters=GPIO_Label
PC14-OSC32_IN.GPIO_Label=GPS_SAFEBOOT
PC14-OSC32_IN.Signal=GPIO_Output
PC15-OSC32_OUT.GPIOParameters=GPIO_Label
PC15-OSC32_OUT.GPIO_Label=DROGUE_CONT
PC15-OSC32_OUT.Signal=GPIO_Input
PC2.GPIOParameters=GPIO_Label
PC2.GPIO_Label=MAIN
PC2.Signal=GPIO_Output
PC3.GPIOParameters=GPIO_Label
PC3.GPIO_Label=MAG_INT
PC3.Signal=GPIO_Input
PC4.GPIOParameters=GPIO_Label
PC4.GPIO_Label=IMU_CS1
PC4.Signal=GPIO_Output
PC5.GPIOParameters=GPIO_Label
PC5.GPIO_Label=LED_STANDBY
PC5.Signal=GPIO_Output
PC6.GPIOParameters=GPIO_Label
PC6.GPIO_Label=RADIO_NRST
PC6.Signal=GPIO_Output
PC7.GPIOParameters=GPIO_Label
PC7.GPIO_Label=FLAP_L_PWM5
PC7.Signal=S_TIM3_CH2
PC8.GPIOParameters=GPIO_Label
PC8.GPIO_Label=FLAP_R_PWM6
PC8.Signal=S_TIM3_CH3
PC9.GPIOParameters=GPIO_Label
PC9.GPIO_Label=GPS_RST
PC9.Signal=GPIO_Output
PD0-OSC_IN.Mode=HSE-External-Oscillator
PD0-OSC_IN.Signal=RCC_OSC_IN
PD1-OSC_OUT.Mode=HSE-External-Oscillator
PD1-OSC_OUT.Signal=RCC_OSC_OUT
PD2.GPIOParameters=GPIO_Label
PD2.GPIO_Label=RADIO_CS
PD2.Signal=GPIO_Output
RCC.HSEDivPLL=RCC_HSE_PREDIV_DIV2
RCC.HSE_VALUE=16000000
RCC.SYSCLKFreq_VALUE=72000000
RCC.SYSCLKSource=RCC_SYSCLKSOURCE_PLLCLK
board=custom

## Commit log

2025-11-18 second commit
2025-11-18 Mostly done with schematic, need to do review
2025-11-28 made new bucks, only 4 warning/errors when importing from schematic
2025-11-28 layout mostly done
2025-11-29 PCB done
2025-11-29 Added gerber, BOM, and parts list csv files for fab.
2025-12-21 commit that was sent to jlcpcb
2026-01-13 start firmware
2026-01-14 first commit for stm32 firmware
2026-01-23 Device ID working
2026-01-23 mag chipID works
2026-01-23 radio test good, need to add nrst to stm32
2026-02-01 working on rev2 on the board, deving out code for flight for stm32 software
2026-03-09 moved to stm32cube vscode extension, v2.0 purchased
2026-03-10 Move to stm32cubeide vscode extension. working
